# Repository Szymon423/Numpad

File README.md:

<div align="center">

# 🔢 Numpad

*A custom-designed numeric keypad project*

</div>

---

## 📖 About

This project is about designing my own Numpad.

> [!NOTE]  
> But not as good as existing solutions

I wanted to do this because I bought a keyboard without a numeric keypad. The project was on my to-do list, waiting until (I make it real) I bought a keyboard with a numeric keypad. Even though I'm the proud owner of a keyboard with a numeric keypad, I wanted to finish it.

---

## 🖼️ Let's have a look

<div align="center">

</div>

---

## 🔧 Hardware

Hardware was designed in **KiCad** around the **RP2040** from Raspberry Pi. I like low-profile keyboards, thus I used **Gateron KS-33** switches with custom keycaps inspired by the **Logitech MX Keys**.

### Additional Renders

<div align="center">

<table>
  <tr>
    <td width="50%"></td>
    <td width="50%"></td>
  </tr>
  <tr>
    <td width="50%"></td>
    <td width="50%"></td>
  </tr>
</table>

</div>

---

## 💻 Software

Software is still in development. 🚧

---

<div align="center">

*Made because of lack of cool and cheap solutions along with ❤️ to tinkering*

</div>

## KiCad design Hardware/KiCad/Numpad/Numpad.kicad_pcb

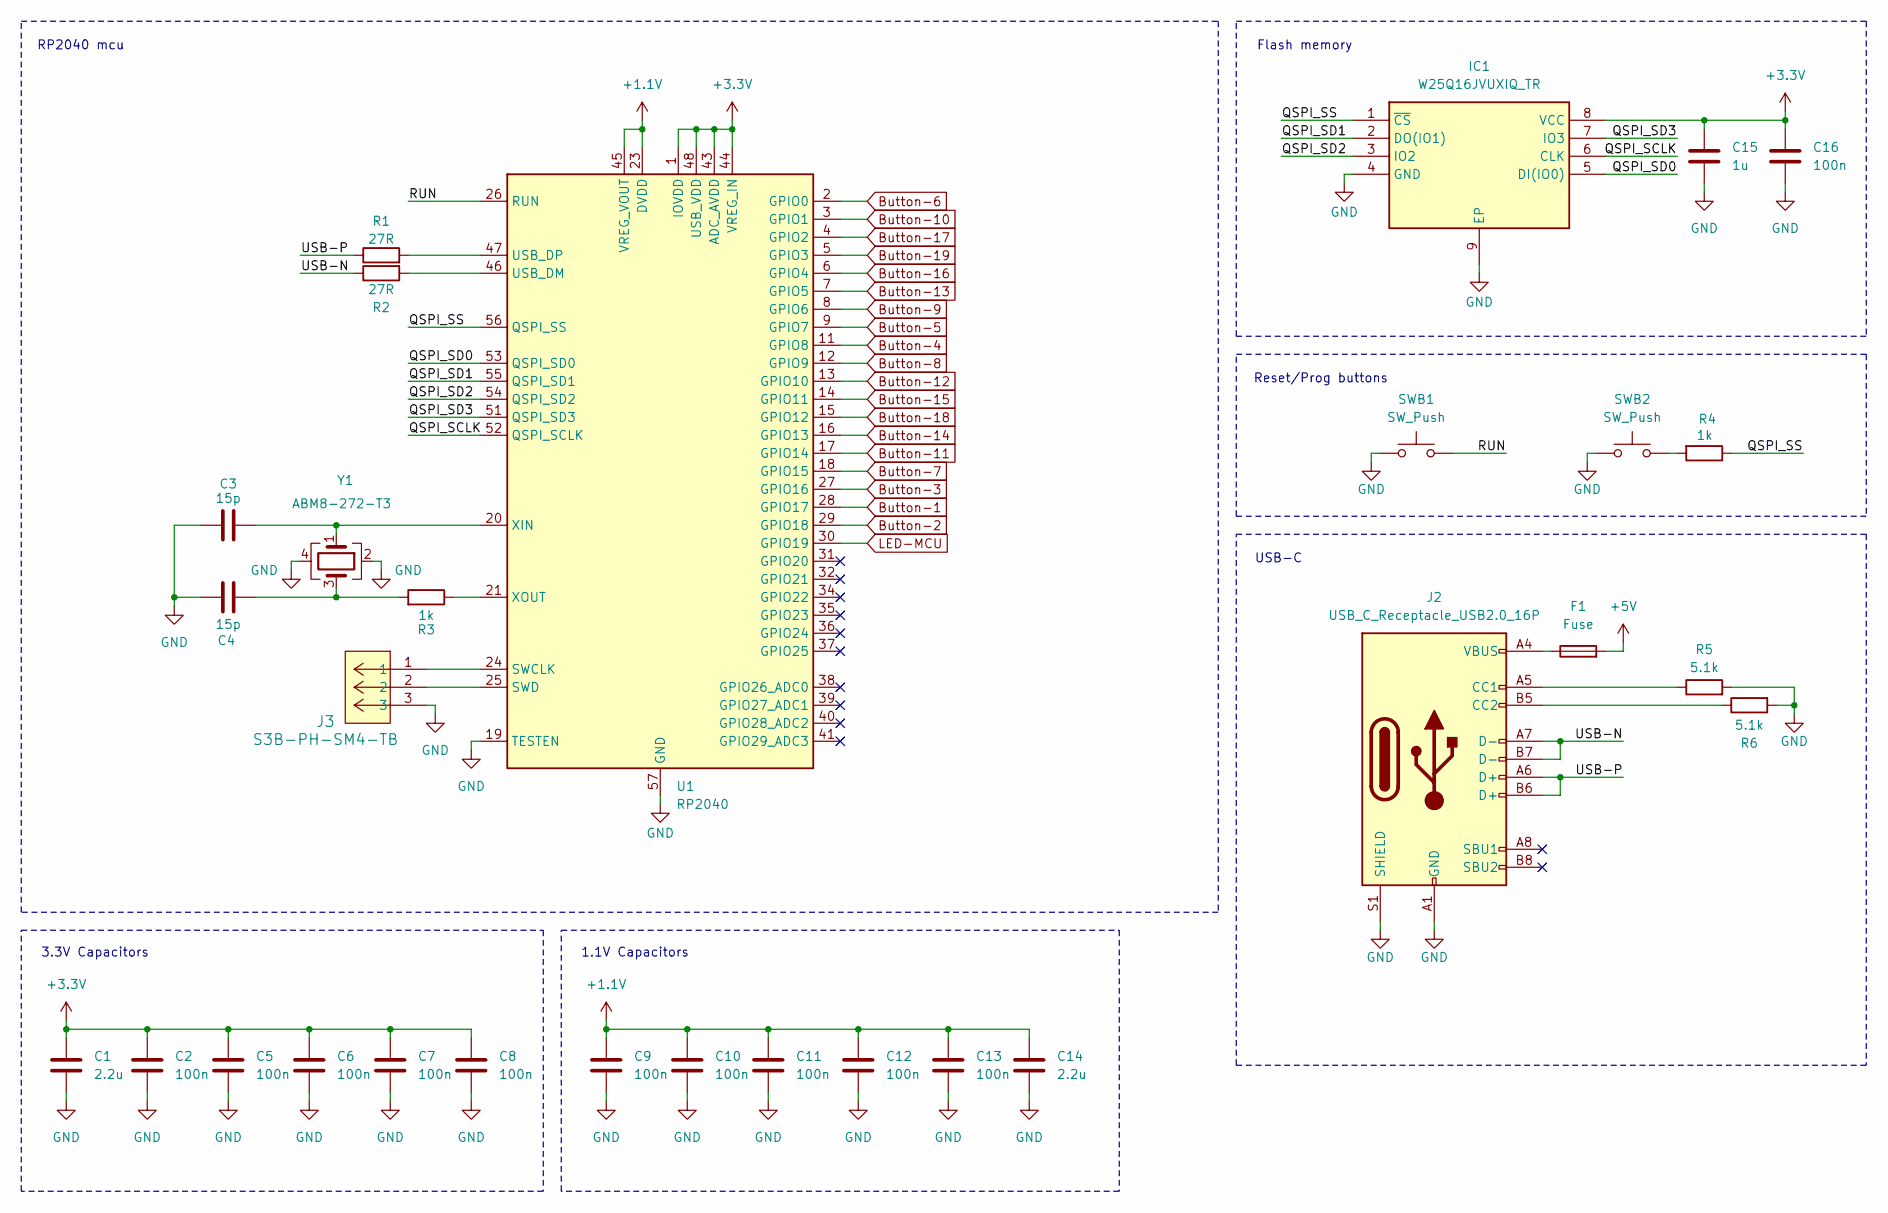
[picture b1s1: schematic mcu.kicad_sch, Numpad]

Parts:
C1, C14: 2.2u; C_0805_2012Metric
C2, C5, C6, C7, C8, C9, C10, C11, C12, C13, C16: 100n; C_0402_1005Metric
C3, C4: 15p; C_0402_1005Metric
C15: 1u; C_0805_2012Metric
F1: Fuse; Fuse_1206_3216Metric
IC1: W25Q16JVUXIQ_TR; Winbond_USON-8-1EP_3x2mm_P0.5mm_EP0.2x1.6mm; Manufacturer_Part_Number W25Q16JVUXIQ TR
J2: USB_C_Receptacle_USB2.0_16P; USB_C_Receptacle_GCT_USB4105-xx-A_16P_TopMnt_Horizontal
J3: S3B-PH-SM4-TB; CONN3_S3B-PH_JST
R1, R2: 27R; R_0402_1005Metric
R3, R4: 1k; R_0402_1005Metric
R5, R6: 5.1k; R_0603_1608Metric
SWB1, SWB2: SW_Push; SW_Tactile_SPST_NO_Straight_CK_PTS636Sx25SMTRLFS
U1: RP2040; QFN-56-1EP_7x7mm_P0.4mm_EP3.2x3.2mm_ThermalVias
Y1: ABM8-272-T3; Crystal_SMD_Abracon_ABM3B-4Pin_5.0x3.2mm

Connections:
+1.1V: C9.1, C10.1, C11.1, C12.1, C13.1, C14.1, U1.23 (DVDD), U1.45 (VREG_VOUT), U1.50 (DVDD)
+3.3V: C1.1, C2.1, C5.1, C6.1, C7.1, C8.1, C15.1, C16.1, IC1.8 (VCC), U1.1 (IOVDD), U1.10 (IOVDD), U1.22 (IOVDD), U1.33 (IOVDD), U1.42 (IOVDD), U1.43 (ADC_AVDD), U1.44 (VREG_IN), U1.48 (USB_VDD), U1.49 (IOVDD); also elsewhere on the board
+5V: F1.2; also elsewhere on the board
/Microcontroller/QSPI_SCLK: IC1.6 (CLK), U1.52 (QSPI_SCLK)
/Microcontroller/QSPI_SD0: IC1.5 (DI(IO0)), U1.53 (QSPI_SD0)
/Microcontroller/QSPI_SD1: IC1.2 (DO(IO1)), U1.55 (QSPI_SD1)
/Microcontroller/QSPI_SD2: IC1.3 (IO2), U1.54 (QSPI_SD2)
/Microcontroller/QSPI_SD3: IC1.7 (IO3), U1.51 (QSPI_SD3)
/Microcontroller/QSPI_SS: IC1.1 (~CS), R4.1, U1.56 (QSPI_SS)
/Microcontroller/RUN: SWB1.2, U1.26 (RUN)
/Microcontroller/USB-N: J2.A7 (D-), J2.B7 (D-), R2.1
/Microcontroller/USB-P: J2.A6 (D+), J2.B6 (D+), R1.1
Button-1: U1.28 (GPIO17); also elsewhere on the board
Button-2: U1.29 (GPIO18); also elsewhere on the board
Button-3: U1.27 (GPIO16); also elsewhere on the board
Button-4: U1.11 (GPIO8); also elsewhere on the board
Button-5: U1.9 (GPIO7); also elsewhere on the board
Button-6: U1.2 (GPIO0); also elsewhere on the board
Button-7: U1.18 (GPIO15); also elsewhere on the board
Button-8: U1.12 (GPIO9); also elsewhere on the board
Button-9: U1.8 (GPIO6); also elsewhere on the board
Button-10: U1.3 (GPIO1); also elsewhere on the board
Button-11: U1.17 (GPIO14); also elsewhere on the board
Button-12: U1.13 (GPIO10); also elsewhere on the board
Button-13: U1.7 (GPIO5); also elsewhere on the board
Button-14: U1.16 (GPIO13); also elsewhere on the board
Button-15: U1.14 (GPIO11); also elsewhere on the board
Button-16: U1.6 (GPIO4); also elsewhere on the board
Button-17: U1.4 (GPIO2); also elsewhere on the board
Button-18: U1.15 (GPIO12); also elsewhere on the board
Button-19: U1.5 (GPIO3); also elsewhere on the board
GND: C1.2, C2.2, C3.1, C4.1, C5.2, C6.2, C7.2, C8.2, C9.2, C10.2, C11.2, C12.2, C13.2, C14.2, C15.2, C16.2, IC1.4 (GND), IC1.9 (EP), J2.A1 (GND), J2.A12 (GND), J2.B1 (GND), J2.B12 (GND), J2.S1 (SHIELD), J3.3, R5.2, R6.2, SWB1.1, SWB2.1, U1.19 (TESTEN), U1.57 (GND), Y1.2, Y1.4; also elsewhere on the board
LED-MCU: U1.30 (GPIO19); also elsewhere on the board
unnamed: C4.2, R3.2, Y1.3
unnamed: F1.1, J2.A4 (VBUS), J2.A9 (VBUS), J2.B4 (VBUS), J2.B9 (VBUS)
unnamed: J2.A5 (CC1), R5.1
unnamed: J2.B5 (CC2), R6.1
unnamed: R4.2, SWB2.2
unnamed: J3.1, U1.24 (SWCLK)
unnamed: J3.2, U1.25 (SWD)
unnamed: R2.2, U1.46 (USB_DM)
unnamed: R1.2, U1.47 (USB_DP)
unnamed: C3.2, U1.20 (XIN), Y1.1
unnamed: R3.1, U1.21 (XOUT)

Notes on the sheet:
RP2040 mcu
Flash memory
3.3V Capacitors
Reset/Prog buttons
1.1V Capacitors
USB-C

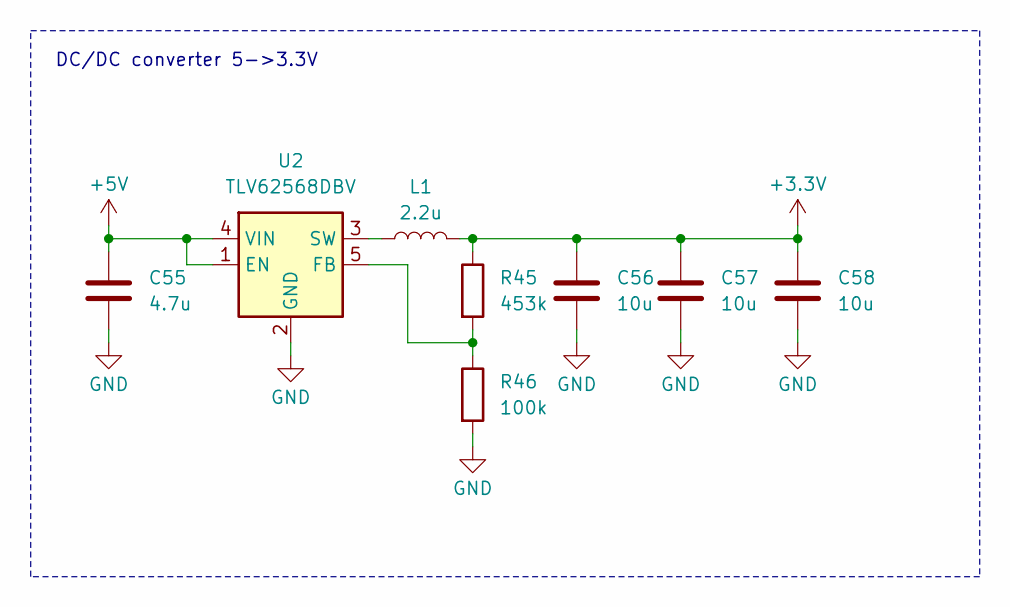
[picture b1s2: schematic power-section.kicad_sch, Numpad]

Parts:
C55: 4.7u; C_0805_2012Metric
C56, C57, C58: 10u; C_0805_2012Metric
L1: 2.2u; L_Ferrocore_DLG-0504
R45: 453k; R_0603_1608Metric
R46: 100k; R_0603_1608Metric
U2: TLV62568DBV; SOT-23-5

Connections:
+3.3V: C56.2, C57.2, C58.2, L1.2, R45.1; also elsewhere on the board
+5V: C55.2, U2.1 (EN), U2.4 (VIN); also elsewhere on the board
GND: C55.1, C56.1, C57.1, C58.1, R46.2, U2.2 (GND); also elsewhere on the board
unnamed: R45.2, R46.1, U2.5 (FB)
unnamed: L1.1, U2.3 (SW)

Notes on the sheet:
DC/DC converter 5->3.3V

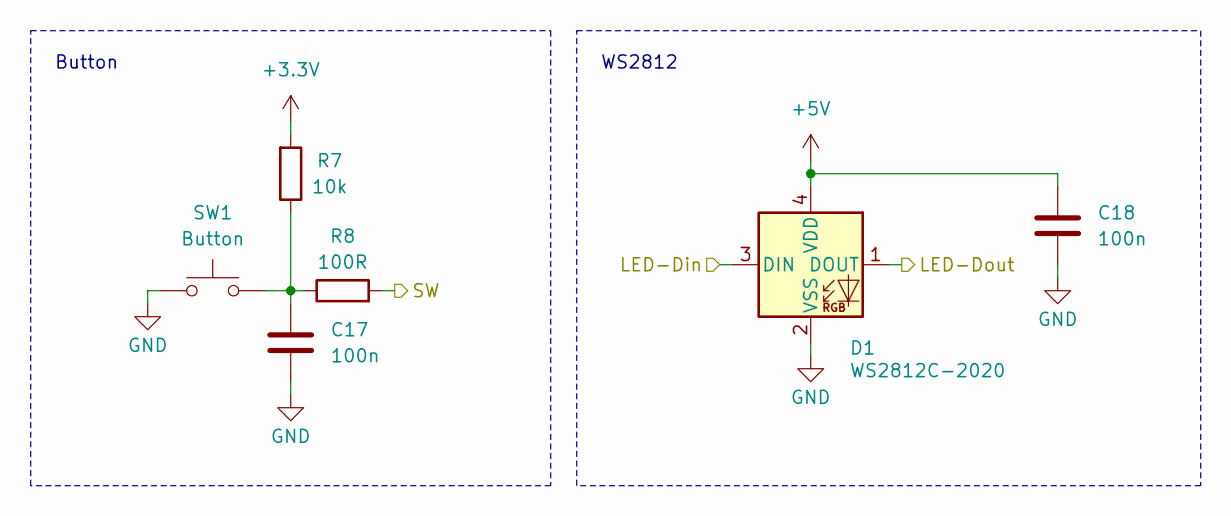
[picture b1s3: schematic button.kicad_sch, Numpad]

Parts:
C17, C18: 100n; C_0603_1608Metric
D1: WS2812C-2020; LED_WS2812B-2020_PLCC4_2.0x2.0mm
R7: 10k; R_0603_1608Metric
R8: 100R; R_0603_1608Metric
SW1: Button; SW_Gateron_LowProfile_THT

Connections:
+3.3V: R7.2; also elsewhere on the board
+5V: C18.1, D1.4 (VDD); also elsewhere on the board
/Buttons/Button1/LED-Din: D1.3 (DIN); also elsewhere on the board
/Buttons/Button1/LED-Dout: D1.1 (DOUT); also elsewhere on the board
Button-1: R8.2; also elsewhere on the board
GND: C17.2, C18.2, D1.2 (VSS), SW1.1; also elsewhere on the board
unnamed: C17.1, R7.1, R8.1, SW1.2

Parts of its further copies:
C19, C20, C21, C22, C23, C24, C25, C26, C27, C28, C29, C30, C31, C32, C33, C34, C35, C36, C37, C38, C39, C40, C41, C42, C43, C44, C45, C46, C47, C48, C49, C50, C51, C52, C53, C54: 100n; C_0603_1608Metric
D2, D3, D4, D5, D6, D7, D8, D9, D10, D11, D12, D13, D14, D15, D16, D17, D18, D19: WS2812C-2020; LED_WS2812B-2020_PLCC4_2.0x2.0mm
R9, R11, R13, R15, R17, R19, R21, R23, R25, R27, R29, R31, R33, R35, R37, R39, R41, R43: 10k; R_0603_1608Metric
R10, R12, R14, R16, R18, R20, R22, R24, R26, R28, R30, R32, R34, R36, R38, R40, R42, R44: 100R; R_0603_1608Metric
SW2, SW3, SW4, SW5, SW6, SW7, SW8, SW9, SW10, SW11, SW12, SW13, SW14, SW15, SW16, SW17, SW18, SW19: Button; SW_Gateron_LowProfile_THT

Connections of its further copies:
+3.3V: R9.2, R11.2, R13.2, R15.2, R17.2, R19.2, R21.2, R23.2, R25.2, R27.2, R29.2, R31.2, R33.2, R35.2, R37.2, R39.2, R41.2, R43.2; also elsewhere on the board
+5V: C20.1, C22.1, C24.1, C26.1, C28.1, C30.1, C32.1, C34.1, C36.1, C38.1, C40.1, C42.1, C44.1, C46.1, C48.1, C50.1, C52.1, C54.1, D2.4 (VDD), D3.4 (VDD), D4.4 (VDD), D5.4 (VDD), D6.4 (VDD), D7.4 (VDD), D8.4 (VDD), D9.4 (VDD), D10.4 (VDD), D11.4 (VDD), D12.4 (VDD), D13.4 (VDD), D14.4 (VDD), D15.4 (VDD), D16.4 (VDD), D17.4 (VDD), D18.4 (VDD), D19.4 (VDD); also elsewhere on the board
/Buttons/Button1/LED-Din: D2.1 (DOUT); also elsewhere on the board
/Buttons/Button1/LED-Dout: D3.3 (DIN); also elsewhere on the board
/Buttons/Button3/LED-Dout: D3.1 (DOUT), D4.3 (DIN)
/Buttons/Button4/LED-Dout: D4.1 (DOUT), D5.3 (DIN)
/Buttons/Button5/LED-Dout: D5.1 (DOUT), D6.3 (DIN)
/Buttons/Button6/LED-Dout: D6.1 (DOUT), D9.3 (DIN)
/Buttons/Button7/LED-Din: D7.3 (DIN), D8.1 (DOUT)
/Buttons/Button8/LED-Din: D8.3 (DIN), D9.1 (DOUT)
/Buttons/Button10/LED-Din: D10.3 (DIN), D13.1 (DOUT)
/Buttons/Button10/LED-Dout: D10.1 (DOUT), D16.3 (DIN)
/Buttons/Button11/LED-Din: D7.1 (DOUT), D11.3 (DIN)
/Buttons/Button11/LED-Dout: D11.1 (DOUT), D12.3 (DIN)
/Buttons/Button12/LED-Dout: D12.1 (DOUT), D13.3 (DIN)
/Buttons/Button14/LED-Din: D14.3 (DIN), D15.1 (DOUT)
/Buttons/Button14/LED-Dout: D14.1 (DOUT), D18.3 (DIN)
/Buttons/Button15/LED-Din: D15.3 (DIN), D16.1 (DOUT)
/Buttons/Button17/LED-Din: D17.3 (DIN), D19.1 (DOUT)
/Buttons/Button17/LED-Dout: D17.1 (DOUT)
/Buttons/Button18/LED-Dout: D18.1 (DOUT), D19.3 (DIN)
Button-2: R10.2; also elsewhere on the board
Button-3: R12.2; also elsewhere on the board
Button-4: R14.2; also elsewhere on the board
Button-5: R16.2; also elsewhere on the board
Button-6: R18.2; also elsewhere on the board
Button-7: R20.2; also elsewhere on the board
Button-8: R22.2; also elsewhere on the board
Button-9: R24.2; also elsewhere on the board
Button-10: R26.2; also elsewhere on the board
Button-11: R28.2; also elsewhere on the board
Button-12: R30.2; also elsewhere on the board
Button-13: R32.2; also elsewhere on the board
Button-14: R34.2; also elsewhere on the board
Button-15: R36.2; also elsewhere on the board
Button-16: R38.2; also elsewhere on the board
Button-17: R40.2; also elsewhere on the board
Button-18: R42.2; also elsewhere on the board
Button-19: R44.2; also elsewhere on the board
GND: C19.2, C20.2, C21.2, C22.2, C23.2, C24.2, C25.2, C26.2, C27.2, C28.2, C29.2, C30.2, C31.2, C32.2, C33.2, C34.2, C35.2, C36.2, C37.2, C38.2, C39.2, C40.2, C41.2, C42.2, C43.2, C44.2, C45.2, C46.2, C47.2, C48.2, C49.2, C50.2, C51.2, C52.2, C53.2, C54.2, D2.2 (VSS), D3.2 (VSS), D4.2 (VSS), D5.2 (VSS), D6.2 (VSS), D7.2 (VSS), D8.2 (VSS), D9.2 (VSS), D10.2 (VSS), D11.2 (VSS), D12.2 (VSS), D13.2 (VSS), D14.2 (VSS), D15.2 (VSS), D16.2 (VSS), D17.2 (VSS), D18.2 (VSS), D19.2 (VSS), SW2.1, SW3.1, SW4.1, SW5.1, SW6.1, SW7.1, SW8.1, SW9.1, SW10.1, SW11.1, SW12.1, SW13.1, SW14.1, SW15.1, SW16.1, SW17.1, SW18.1, SW19.1; also elsewhere on the board
LED-MCU: D2.3 (DIN); also elsewhere on the board
unnamed: C19.1, R9.1, R10.1, SW2.2
unnamed: C21.1, R11.1, R12.1, SW3.2
unnamed: C23.1, R13.1, R14.1, SW4.2
unnamed: C25.1, R15.1, R16.1, SW5.2
unnamed: C27.1, R17.1, R18.1, SW6.2
unnamed: C29.1, R19.1, R20.1, SW7.2
unnamed: C31.1, R21.1, R22.1, SW8.2
unnamed: C33.1, R23.1, R24.1, SW9.2
unnamed: C35.1, R25.1, R26.1, SW10.2
unnamed: C37.1, R27.1, R28.1, SW11.2
unnamed: C39.1, R29.1, R30.1, SW12.2
unnamed: C41.1, R31.1, R32.1, SW13.2
unnamed: C43.1, R33.1, R34.1, SW14.2
unnamed: C45.1, R35.1, R36.1, SW15.2
unnamed: C47.1, R37.1, R38.1, SW16.2
unnamed: C49.1, R39.1, R40.1, SW17.2
unnamed: C51.1, R41.1, R42.1, SW18.2
unnamed: C53.1, R43.1, R44.1, SW19.2

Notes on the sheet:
Button
WS2812

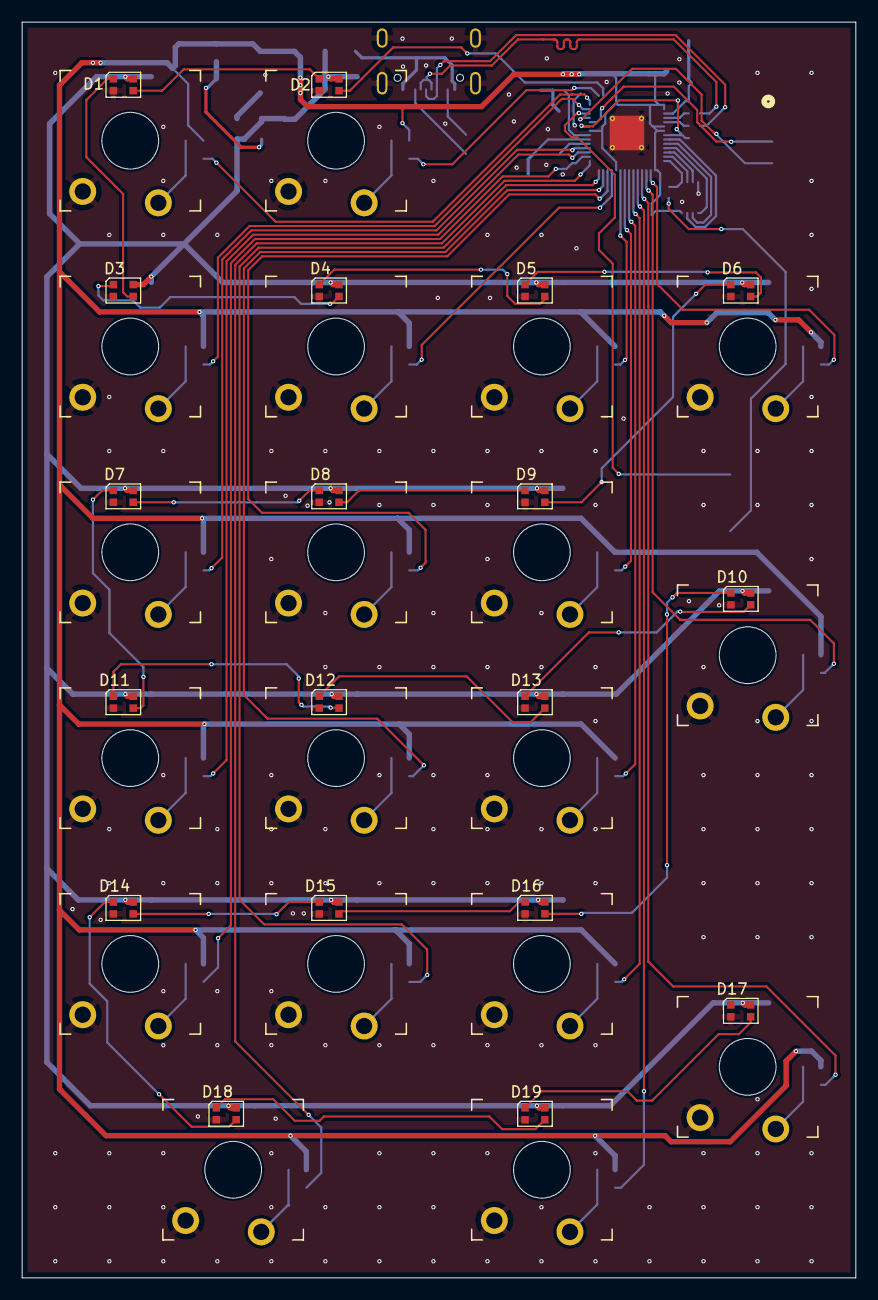
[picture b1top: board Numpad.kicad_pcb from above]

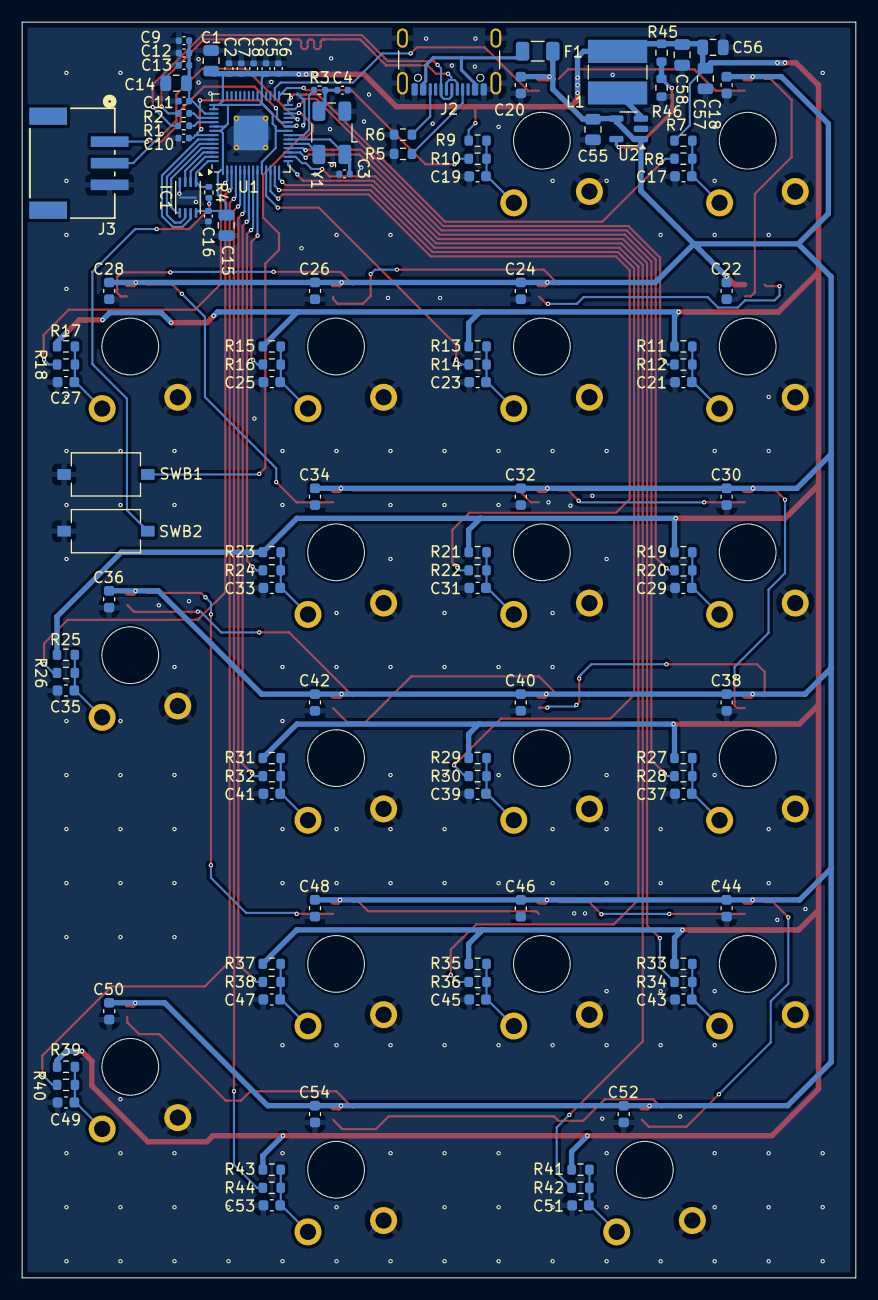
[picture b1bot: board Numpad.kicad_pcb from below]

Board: 2 copper layers, 77.2 x 116.2 mm, 152 parts (114 on the bottom side), 83 nets.

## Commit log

2024-11-16 found working pio library for neopixel
2024-11-16 found working library for neopixel
2024-11-16 nothing to look at
2024-11-16 added hardware stuff
2024-11-17 added something which will not compile, and not work but it is a good start into hid
2024-11-17 readme update
2025-10-30 A little update on hardware
